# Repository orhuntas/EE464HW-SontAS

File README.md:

# EE464HW-SontAS
EE464 Hardware Project Repository for Şönt A.Ş.

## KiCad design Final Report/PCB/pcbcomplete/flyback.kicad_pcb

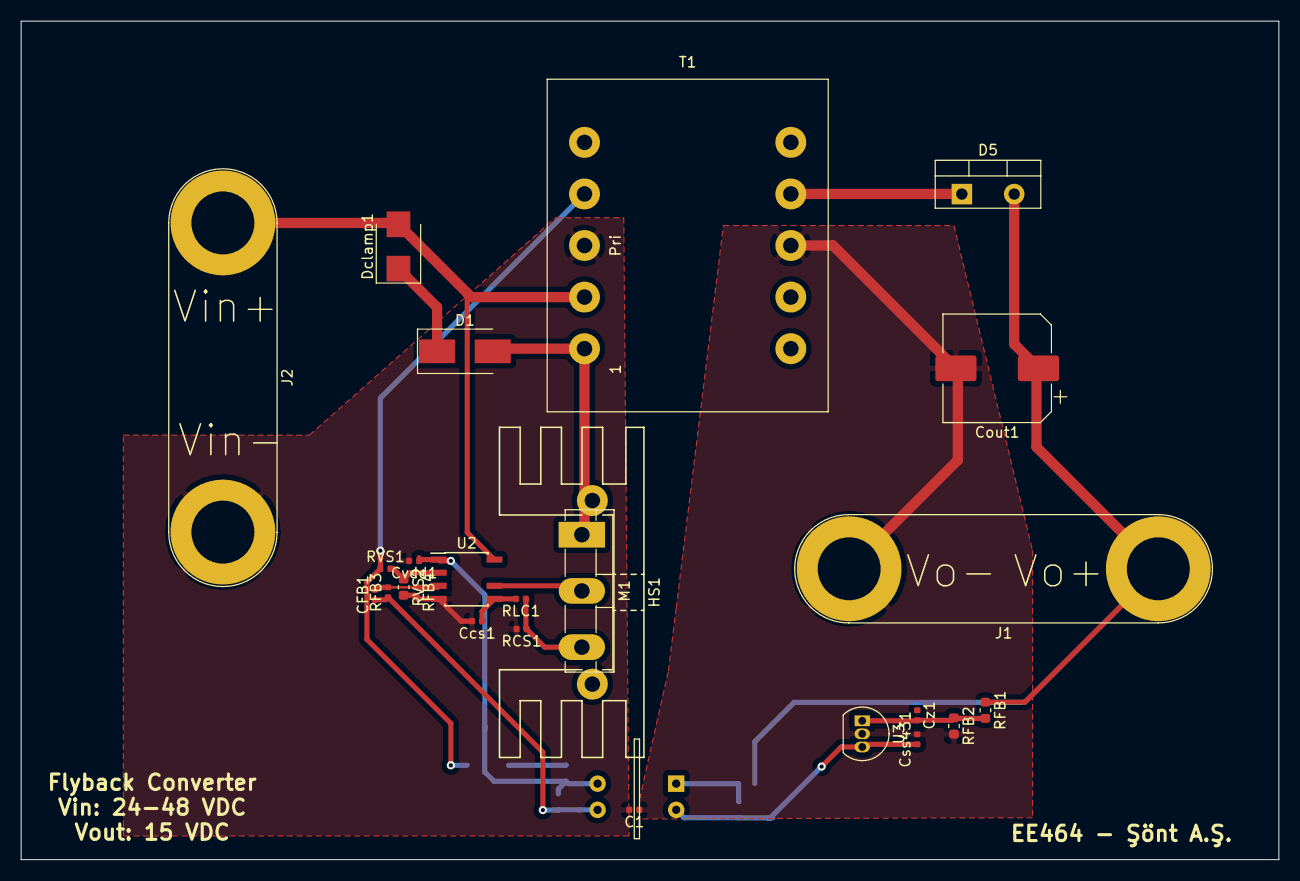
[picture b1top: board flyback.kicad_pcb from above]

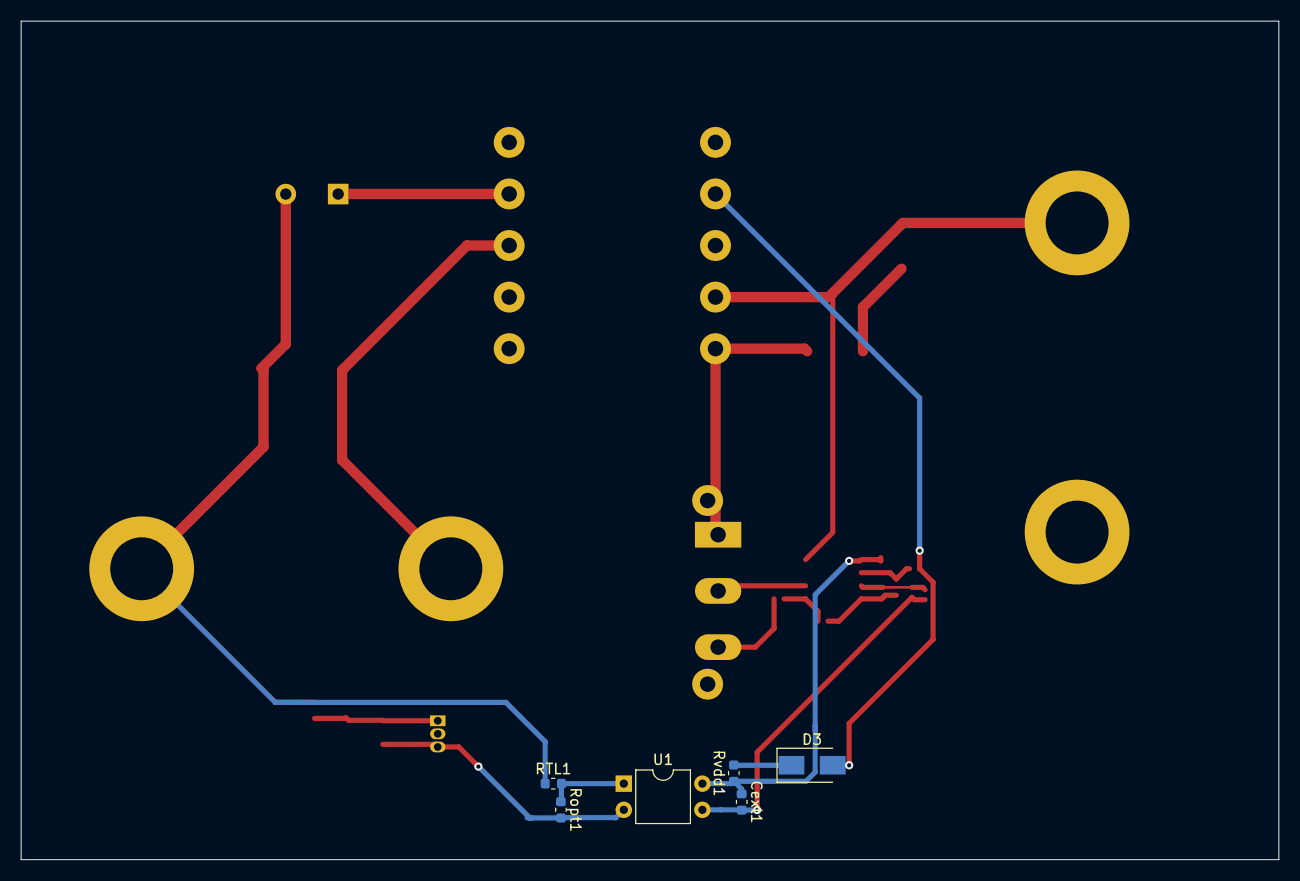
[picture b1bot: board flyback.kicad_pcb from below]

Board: 2 copper layers, 121.9 x 81.3 mm, 31 parts (6 on the bottom side), 19 nets.

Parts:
C1: C; C_0402_1005Metric
CFB1: C; C_0402_1005Metric
Ccs1: C; C_0402_1005Metric
Cext1: C; C_0603_1608Metric
Cout1: CP1; CP_Elec_10x10
Css431: C; C_0402_1005Metric
Cvdd1: C; C_0402_1005Metric
Cz1: C; C_0402_1005Metric
D1: D; D_SMB_Handsoldering
D3: B120-E3; D_SMA
D5: D_Schottky; TO-220-2_Vertical
Dclamp1: D_Zener; D_SMB
HS1: Heatsink; Heatsink_Stonecold_HS-132_32x14mm_2xFixation1.5mm
J1, J2: Conn_01x02; Banana_Jack_2Pin
M1: MNMOS; TO-3P-3_Vertical
RCS1: R; R_0402_1005Metric
RFB1, RFB2: R; R_0603_1608Metric
RFB3, RFB4: R; R_0402_1005Metric
RLC1: R; R_0402_1005Metric
RTL1: R; R_0603_1608Metric
RVS1: R; R_0402_1005Metric
RVS2: R; R_0603_1608Metric
Ropt1: R; R_0603_1608Metric
Rvdd1: R; R_0603_1608Metric
T1: Transformer_1P_2S; Transformer_CHK_EI30-2VA_2xSec
U1: SFH617A-1; DIP-4_W7.62mm
U2: UCC28740; SOIC-8-N7_3.9x4.9mm_P1.27mm
U3: TL431LP; TO-92_Inline

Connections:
+48V: Dclamp1.2, J2.1, T1.1, U2.8
/OPTO+: RTL1.2, Ropt1.1, U1.1
/OPTO-: Css431.1, Cz1.1, Ropt1.2, U1.2, U3.3
/Vout+: Cout1.1, D5.2, J1.1, RFB1.1, RTL1.1
GND: C1.2, Ccs1.2, Cvdd1.2, J2.2, RCS1.2, RFB4.2, RVS2.2, T1.6, U2.4
GND2: C1.1, Cout1.2, Css431.2, J1.2, RFB2.2, T1.4, U3.2
unnamed: CFB1.1, Cext1.2, RFB3.1, U1.3
unnamed: CFB1.2, RFB3.2, RFB4.1, U2.3
unnamed: Ccs1.1, RLC1.2, U2.5
unnamed: Cext1.1, Cvdd1.1, Rvdd1.1, U1.4, U2.1
unnamed: Cz1.2, RFB1.2, RFB2.1, U3.1
unnamed: D1.1, Dclamp1.1
unnamed: D1.2, M1.1, T1.2
unnamed: D3.1, Rvdd1.2
unnamed: D3.2, RVS1.1, T1.5
unnamed: D5.1, T1.3
unnamed: M1.2, U2.6
unnamed: M1.3, RCS1.1, RLC1.1
unnamed: RVS1.2, RVS2.1, U2.2

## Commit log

2020-03-06 started on the project
    discussion about ICs are dıne,
    component calculations are made,
    research on magnetic design,
    created simulation model for inspection
2020-03-06 Magnetic Design Application Note
2020-03-12 Calculation Table is created
    Calculation Table is created and uploaded.
2020-03-23 simulation report
    done collectively on overleaf, hence no additional commmits
2020-03-23 Simulation Report is uploaded.
    Simulation Report is completed collaboratively.
2020-03-27 core
2020-06-02 KiCad model of the converter for PCB design is created
    The flyback converter is modeled in KiCad for the PCB design. The circuit model of the flyback converter model with the selected controller IC is drawn in KiCad and footprint assignment for the used 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
2020-06-02 The designed compensator is simulated in LTSpice
    The designed type 3 A compensator is drawn and simulated in LTSpice for different step changes in the load and also in the input voltage.
    Two LTSpice models are created to simulate the step change in the load from half to full load, and to simulate the step change in the input voltage from 48V to 24V.
2020-06-02 Create parameters.xlsx
    An excel sheet is created to make the calculations of the copper length and resistances of the primary and the secondary windings of the transformer iterable with different core and cable selections.
2020-06-02 Compensator is designed for flyback converter
    A type 3 A compensator is designed for the flyback converter.
    The transfer function and the loop gain of the compensated flyback converter with the designed compensator is obtained.
    The MATLAB scripts to obtain the bode plots are created.
2020-06-02 Simulink model of the nonideal flyback converter
    Simulink model for the nonlideal flyback converter is created with the calculated nonidealities.
2020-06-23 pcb design
    pcb design complete including layout and 3D view. BOM should be edited.
2020-06-24 DATASHEETS
2020-06-24 final additions
    pcb design revisited, gerber files, 3D views generated, images are added, final additions to the report
2020-06-24 final report files
    report was written in overleaf, copied the files to github repo
